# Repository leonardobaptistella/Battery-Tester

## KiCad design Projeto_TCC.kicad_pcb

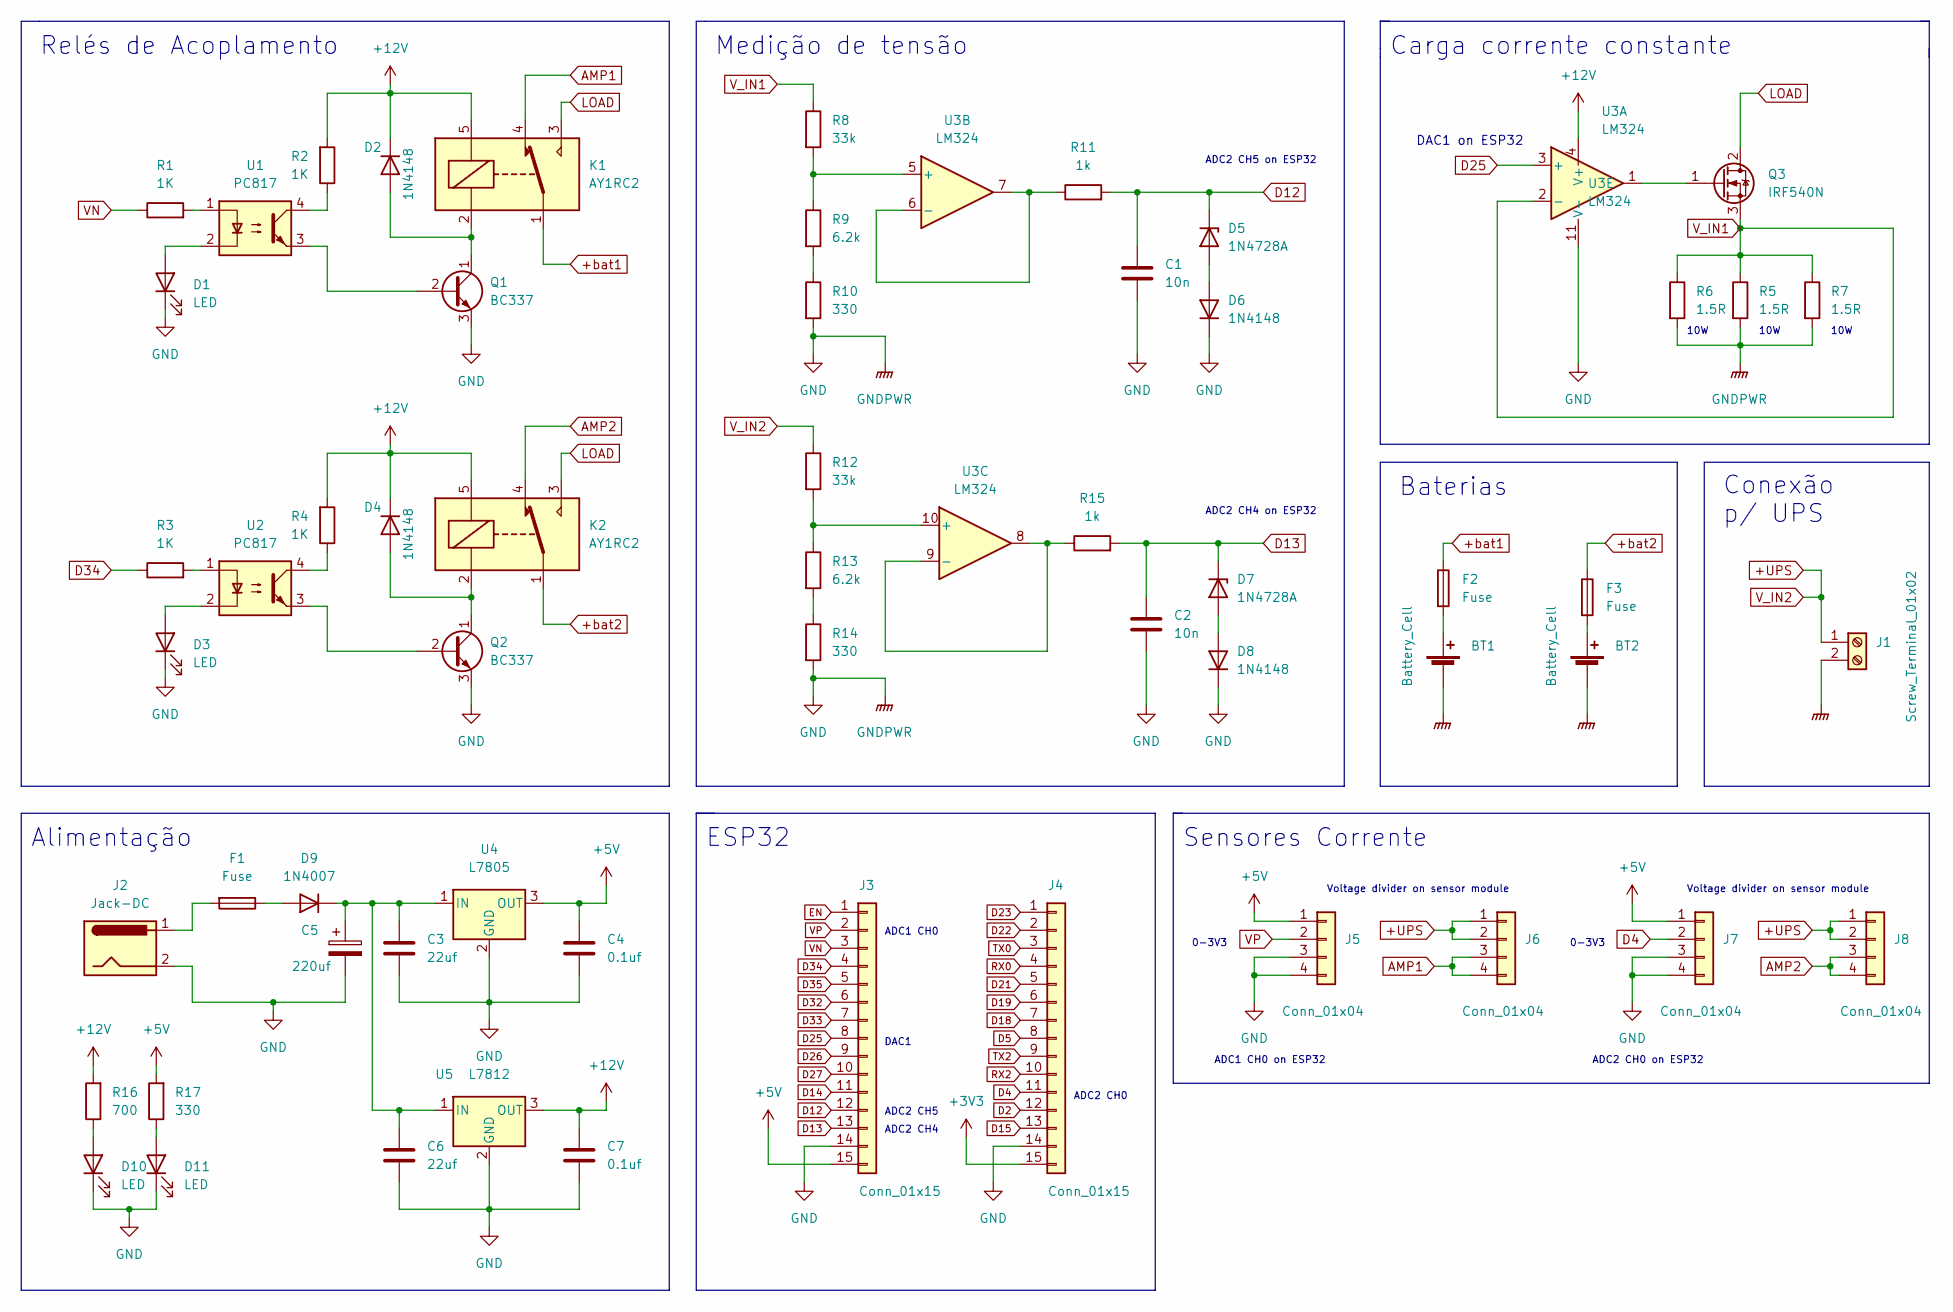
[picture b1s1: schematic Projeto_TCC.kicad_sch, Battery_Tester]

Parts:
BT1, BT2: Battery_Cell; TerminalBlock_Altech_AK300-2_P5.00mm
C1, C2: 10n; C_Disc_D4.3mm_W1.9mm_P5.00mm
C3, C6: 22uf; C_Disc_D4.3mm_W1.9mm_P5.00mm
C4, C7: 0.1uf; C_Disc_D4.3mm_W1.9mm_P5.00mm
C5: 220uf; CP_Radial_D8.0mm_P3.50mm
D1, D3, D10, D11: LED; LED_D3.0mm
D2, D4, D6, D8: 1N4148; D_DO-35_SOD27_P7.62mm_Horizontal
D5, D7: 1N4728A; D_DO-41_SOD81_P10.16mm_Horizontal
D9: 1N4007; D_DO-41_SOD81_P10.16mm_Horizontal
F1, F2, F3: Fuse; Fuseholder_Cylinder-5x20mm_Stelvio-Kontek_PTF78_Horizontal_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
J1: Screw_Terminal_01x02; TerminalBlock_Altech_AK300-2_P5.00mm
J2: Jack-DC; BarrelJack_Horizontal
J3, J4: Conn_01x15; PinHeader_1x15_P2.54mm_Vertical
J5, J6, J7, J8: Conn_01x04; PinHeader_1x04_P2.54mm_Vertical
K1, K2: AY1RC2; Relay_SPDT_SANYOU_SRD_Series_Form_C
Q1, Q2: BC337; TO-92_Inline
Q3: IRF540N; TO-220-3_Vertical
R1, R2, R3, R4: 1K; R_Axial_DIN0207_L6.3mm_D2.5mm_P7.62mm_Horizontal
R5, R6, R7: 1.5R; R_Axial_DIN0617_L17.0mm_D6.0mm_P30.48mm_Horizontal
R8, R12: 33k; R_Axial_DIN0207_L6.3mm_D2.5mm_P7.62mm_Horizontal
R9, R13: 6.2k; R_Axial_DIN0207_L6.3mm_D2.5mm_P7.62mm_Horizontal
R10, R14, R17: 330; R_Axial_DIN0207_L6.3mm_D2.5mm_P7.62mm_Horizontal
R11, R15: 1k; R_Axial_DIN0207_L6.3mm_D2.5mm_P7.62mm_Horizontal
R16: 700; R_Axial_DIN0207_L6.3mm_D2.5mm_P7.62mm_Horizontal
U1, U2: PC817; DIP-4_W7.62mm
U3: LM324; DIP-14_W7.62mm_LongPads
U4: L7805; TO-218-3_Vertical
U5: L7812; TO-218-3_Vertical

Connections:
+3V3: J4.15
+5V: C4.1, J3.15, J5.1, J7.1, R17.2, U4.3 (OUT)
+12V: C7.1, D2.1 (K), D4.1 (K), K1.5, K2.5, R2.2, R4.2, R16.2, U3.4 (V+), U5.3 (OUT)
+UPS: J1.1, J6.1, J6.2, J8.1, J8.2, R12.1
+bat1: F2.1, K1.1
+bat2: F3.1, K2.1
AMP1: J6.3, J6.4, K1.4
AMP2: J8.3, J8.4, K2.4
D2: J4.12
D4: J4.11, J7.2
D5: J4.8
D12: C1.1, D5.1 (K), J3.12, R11.2
D13: C2.1, D7.1 (K), J3.13, R15.2
D14: J3.11
D15: J4.13
D18: J4.7
D19: J4.6
D21: J4.5
D22: J4.2
D23: J4.1
D25: J3.8, U3.3 (+)
D26: J3.9
D27: J3.10
D32: J3.6
D33: J3.7
D34: J3.4, R3.1
D35: J3.5
EN: J3.1
LOAD: K1.3, K2.3, Q3.2 (D)
unnamed: BT1.1 (+), F2.2
unnamed: BT2.1 (+), F3.2
unnamed: C3.1, C5.1, C6.1, D9.1 (K), U4.1 (IN), U5.1 (IN)
unnamed: D1.2 (A), U1.2
unnamed: D2.2 (A), K1.2, Q1.1 (C)
unnamed: D3.2 (A), U2.2
unnamed: D4.2 (A), K2.2, Q2.1 (C)
unnamed: D5.2 (A), D6.2 (A)
unnamed: D7.2 (A), D8.2 (A)
unnamed: D9.2 (A), F1.1
unnamed: D10.2 (A), R16.1
unnamed: D11.2 (A), R17.1
unnamed: F1.2, J2.1
unnamed: Q1.2 (B), U1.3
unnamed: Q2.2 (B), U2.3
unnamed: Q3.1 (G), U3.1
unnamed: R1.2, U1.1
unnamed: R2.1, U1.4
unnamed: R3.2, U2.1
unnamed: R4.1, U2.4
unnamed: R8.2, R9.1, U3.5 (+)
unnamed: R9.2, R10.1
unnamed: R11.1, U3.6 (-), U3.7
unnamed: R12.2, R13.1, U3.10 (+)
unnamed: R13.2, R14.1
unnamed: R15.1, U3.8, U3.9 (-)
RX0: J4.4
RX2: J4.10
TX0: J4.3
TX2: J4.9
VN: J3.3, R1.1
VP: J3.2, J5.2
V_IN1: Q3.3 (S), R5.1, R6.1, R7.1, R8.1, U3.2 (-)

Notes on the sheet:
Carga corrente constante
Voltage divider on sensor module
Alimentação
ADC2 CH5 on ESP32
Medição de tensão
ADC2 CH0
ADC1 CH0 on ESP32
Baterias
Sensores Corrente
10W
DAC1 on ESP32
ADC1 CH0
ESP32
ADC2 CH4
Conexão p/ UPS
Relés de Acoplamento
0-3V3
ADC2 CH4 on ESP32
ADC2 CH0 on ESP32
DAC1
ADC2 CH5

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
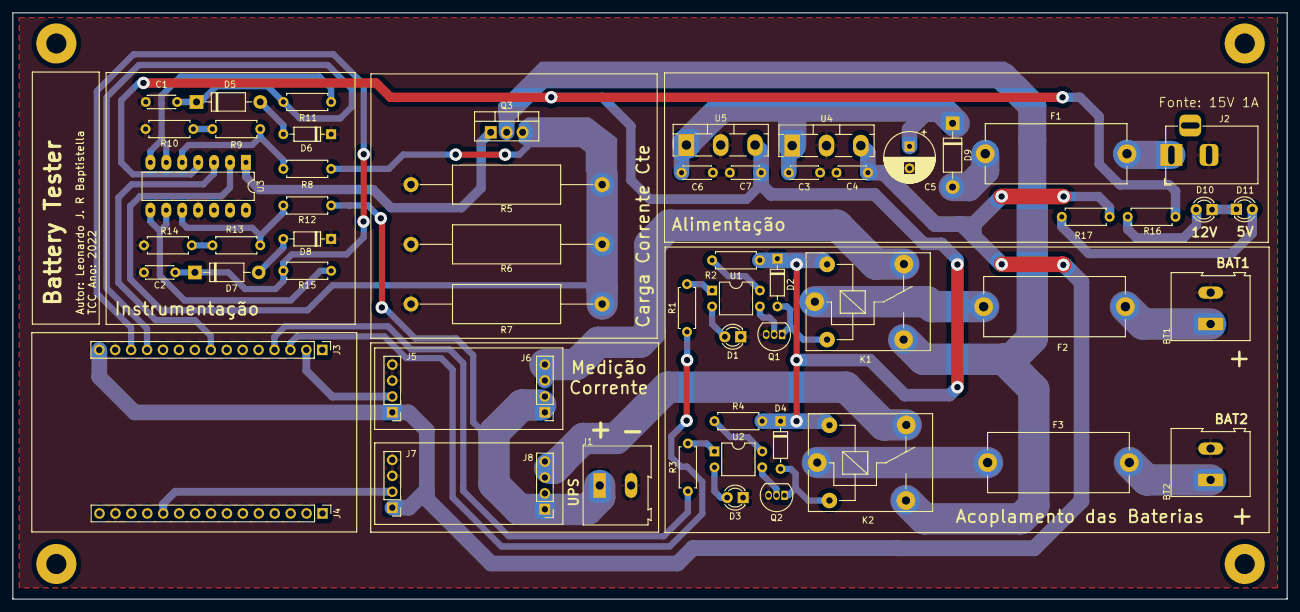
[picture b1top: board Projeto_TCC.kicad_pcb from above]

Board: 2 copper layers, 203.2 x 93.5 mm, 58 parts (0 on the bottom side), 43 nets.

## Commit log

2022-05-26 Battery tester TCC
